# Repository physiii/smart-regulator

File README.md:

## This repository contains the code, schematic, and layout for a wifi controlled and monitored 5V 3A regulator that works with __open-automation__.

### open-automation is made from a cohesive set of web languages. NodeJS for general processing, socket.io for bidirectional communication. NodeJS is used for generating, setting, and retreiving model (mongodb) data. Websockets is used for transport on microcontrollers. Live token based streaming with JSMPEG decoding on camera devices. Web interface is angularjs. Android app for location beacons. Now supports streaming from behind routers, this is done through websockets; so no port forwarding necessary!

### Can be used for controlling cameras, dead bolts, garage openers, lights, thermostats, media, glass break, and a customizable alert system.

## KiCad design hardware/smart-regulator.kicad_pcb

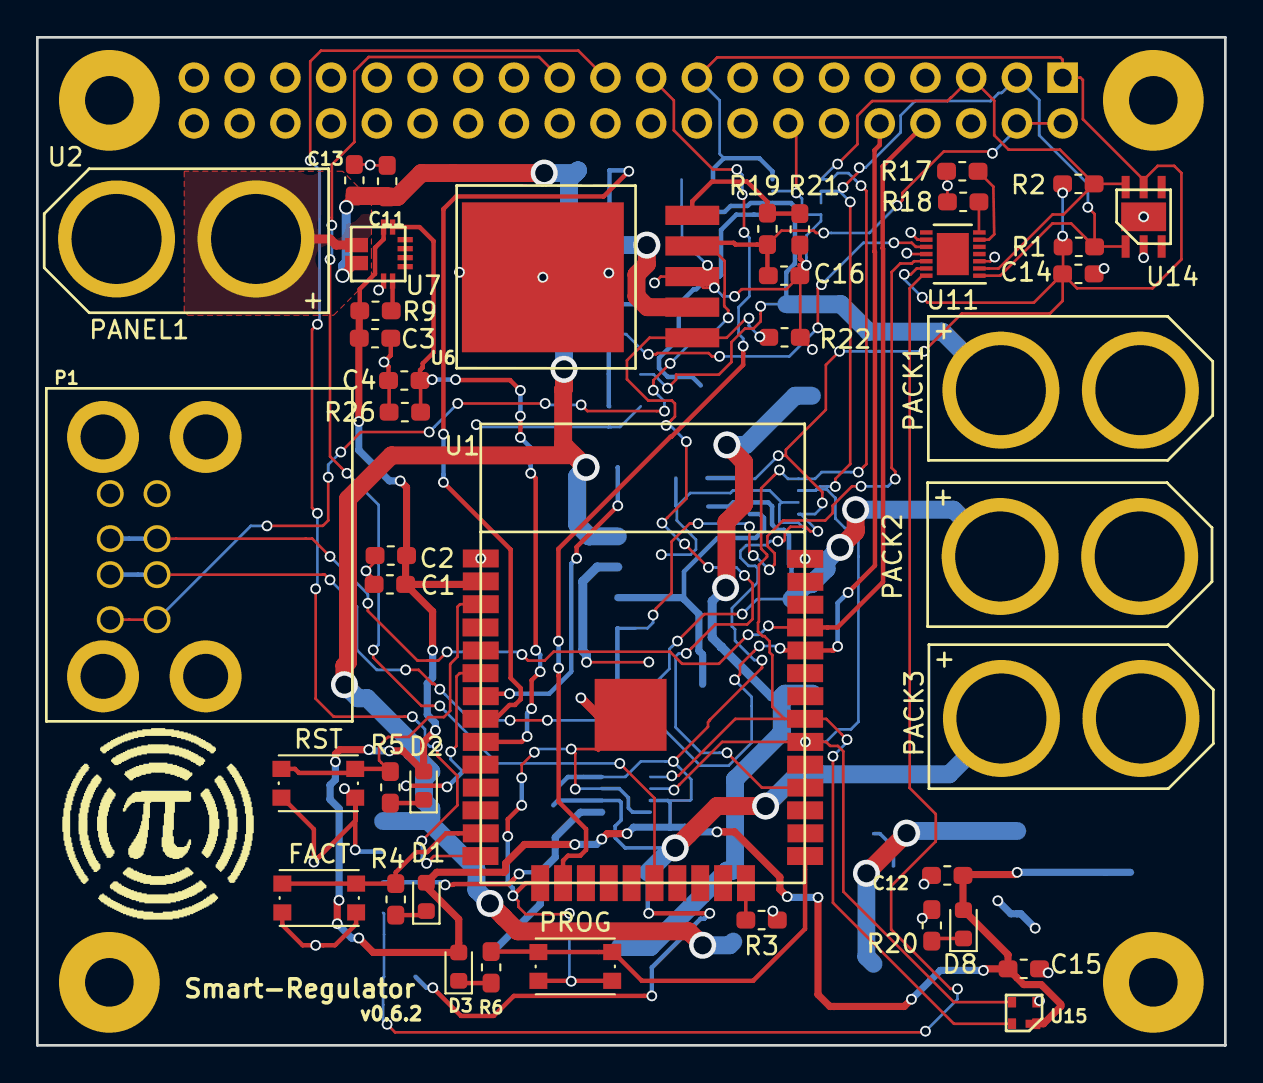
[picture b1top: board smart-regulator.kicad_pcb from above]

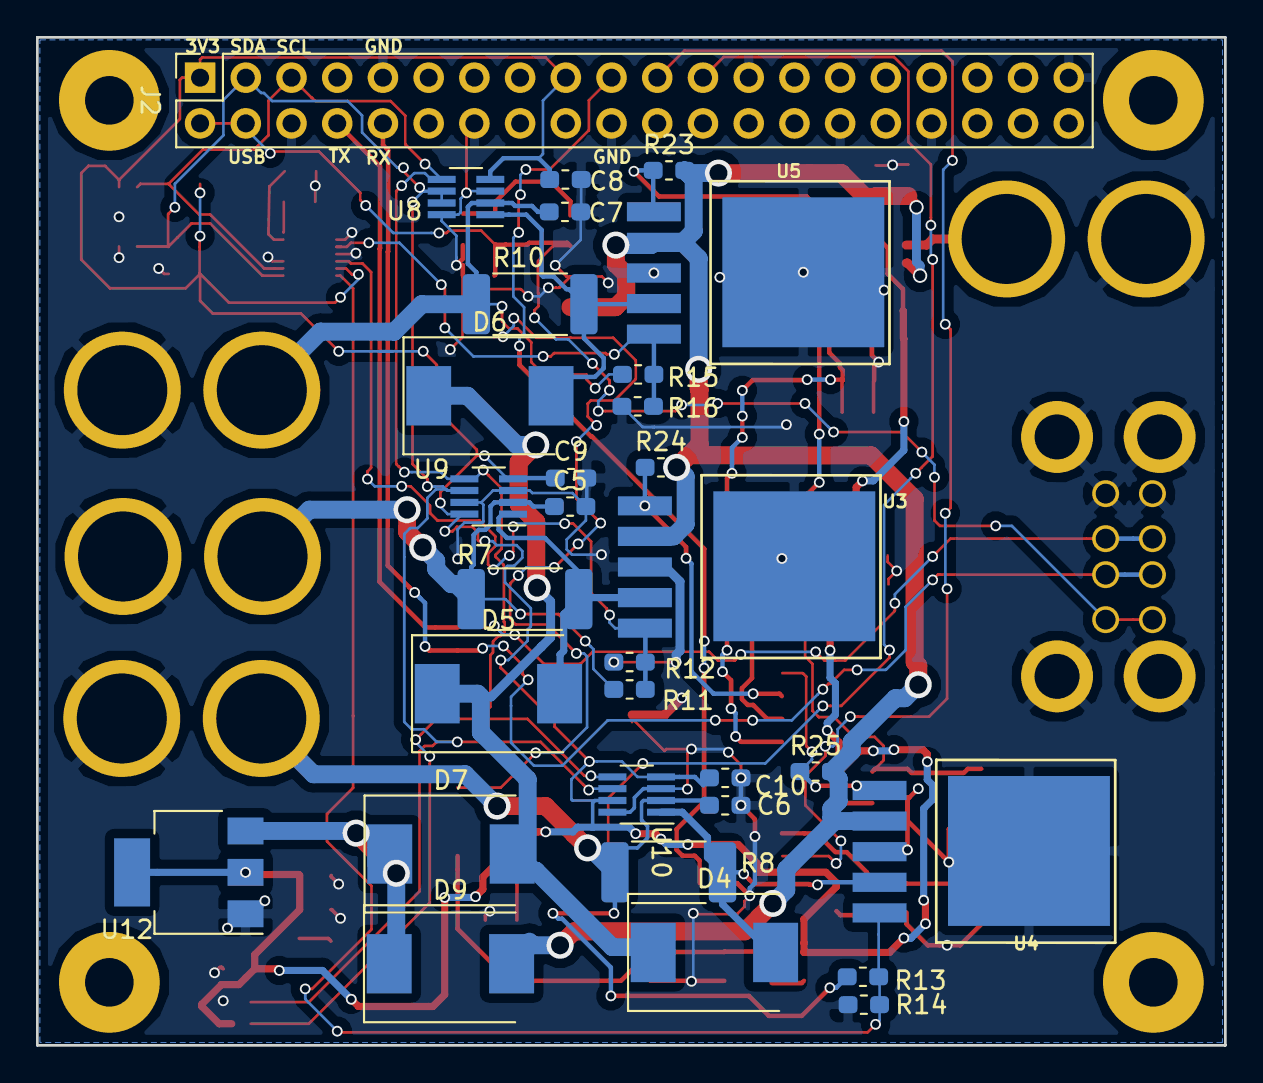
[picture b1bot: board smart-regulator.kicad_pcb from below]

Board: 2 copper layers, 66.0 x 56.0 mm, 75 parts (31 on the bottom side), 40 nets.

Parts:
C1, C4, C5, C6, C7, C11, C16: C_10uF; C_0603_1608Metric_Pad1.05x0.95mm_HandSolder
C2, C13: C_1uF; C_0603_1608Metric_Pad1.05x0.95mm_HandSolder
C3, C8, C9, C10, C14, C15: C_0.1uF; C_0603_1608Metric_Pad1.05x0.95mm_HandSolder
C12: 4.7uF; C_0603_1608Metric_Pad1.05x0.95mm_HandSolder
D1, D2, D3, D8: LED-0603-R; LED_0603_1608Metric_Pad0.88x0.95mm_HandSolder
D4, D5, D6, D7, D9: D; D_SMC
FACT: SW_PUSH; SW_SPST_KMR2
J2: Conn_02x20_Odd_Even; PinSocket_2x20_P2.54mm_Vertical
LOGO: pyfi_symbol
P1: USB_A_2
PACK1, PACK2, PACK3: CONN_01X02; XT60
PANEL1: CONN_01X02; XT60
PROG: SW_PUSH; SW_SPST_KMR2
R1, R2, R3, R4, R5, R6, R11, R12, R13, R14, R15, R16, R19, R20, R21, R22, R23, R24, R25, R26: R_10k; R_0603_1608Metric_Pad1.05x0.95mm_HandSolder
R7, R8, R10: R_10m; R_2512_6332Metric_Pad1.52x3.35mm_HandSolder
R9, R17, R18: R_1k; R_0603_1608Metric_Pad1.05x0.95mm_HandSolder
RST: SW_PUSH; SW_SPST_KMR2
U1: ESP-WROOM-32
U2: housing-mounts; Pi Mount
U3, U4, U5, U6: MIC29302; Regulator-LM2576
U7: ACS712ELCTR-05B-T_NRND; ACS711
U8, U9, U10: Power-Monitor-INA219; SOT-23-8_Handsoldering
U11: DAC; DFN-14-1EP_3x3mm_P0.4mm_EP1.78x2.35mm
U12: ZLDO1117G33TA; SOT-223
U14: SI7006-A20; SI7020-A20
U15: TSL45315CL; LIGHT-SENSOR-TSL45315CL

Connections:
3V3: C1.1, C2.1, C3.1, C8.2, C9.2, C10.2, C12.1, C14.1, C15.1, D1.2, D2.2, D3.2, D8.2, J2.1, J2.17, R1.2, R2.2, R9.1, U1.2, U7.12, U8.4, U9.4, U9.8, U10.4, U10.7, U11.13, U12.2, U12.4, U14.5, U15.1
/EN: R5.2, RST.1, U1.3
/FACTORY: FACT.1, R4.2, U1.13
/I02: R3.2, U1.24
/PACK1: C7.1, PACK1.1, R10.2, R15.1, U8.2
/PACK2: C5.1, PACK2.1, R7.2, R11.1, U9.2
/PACK3: C6.1, PACK3.1, R8.2, R13.1, U10.2
/PROG: PROG.1, R6.2, U1.25
/Power/OUT1: R15.2, R16.1, U5.5, U11.10
/Power/OUT2: R11.2, R12.1, U3.5, U11.12
/Power/OUT3: R13.2, R14.1, U4.5, U11.14
/Power/REG1_PRE: D6.2, R10.1, U5.4, U8.1
/Power/REG2_PRE: D5.2, R7.1, U3.4, U9.1
/Power/REG3_PRE: D4.2, R8.1, U4.4, U10.1
/Power/REG_POWER: C11.1, C13.1, D9.2, R23.2, R24.2, R25.2, U3.2, U4.2, U5.2, U6.2, U7.3
/REG1_EN: R23.1, U1.8, U5.1
/REG2_EN: R24.1, U1.7, U3.1
/REG3_EN: R25.1, U1.6, U4.1
/RXD: J2.10, P1.4, P1.6, U1.34
/SCL: J2.5, R2.1, U1.31, U8.5, U9.5, U10.5, U11.2, U14.6, U15.4
/SDA: J2.3, R1.1, U1.30, U8.6, U8.7, U9.6, U10.6, U11.1, U14.1, U15.3
/TXD: J2.8, P1.3, P1.5, U1.35
/USB_EN: R22.1, U1.28, U6.1
/V_MAIN: D4.1, D5.1, D6.1, D7.2
/V_PANEL: PANEL1.1, U7.1
/V_USB: C16.1, J2.2, J2.4, P1.2, R19.1, U6.4
/microcontroller/MISO: J2.21, U1.14
/microcontroller/MOSI: J2.19, U1.16
/microcontroller/SCLK: J2.23, U1.20
GND: C1.2, C2.2, C3.2, C4.2, C5.2, C6.2, C7.2, C8.1, C9.1, C10.1, C11.2, C12.2, C13.2, C14.2, C15.2, C16.2, FACT.2, J2.6, J2.9, J2.14, J2.20, J2.25, J2.30, J2.34, J2.39, P1.1, P1.7, PACK1.2, PACK2.2, PACK3.2, PANEL1.2, PROG.2, R3.1, R12.2, R14.2, R16.2, R17.2, R18.2, R20.2, R21.2, R22.2, R26.2, RST.2, U1.1, U3.3, U4.3, U5.3, U6.3, U7.5, U8.3, U8.8, U9.3, U9.7, U10.3, U10.8, U11.3, U11.9, U11.11, U12.1, U14.2, U15.2
MAIN_CURRENT_SENSE: C4.1, R26.1, U1.9, U7.11
unnamed: D1.1, R4.1
unnamed: D2.1, R5.1
unnamed: D3.1, R6.1
unnamed: D7.1, D9.1, U12.3
unnamed: D8.1, R20.1
unnamed: R9.2, U7.6
unnamed: R17.1, U11.6
unnamed: R18.1, U11.7
unnamed: R19.2, R21.1, U6.5

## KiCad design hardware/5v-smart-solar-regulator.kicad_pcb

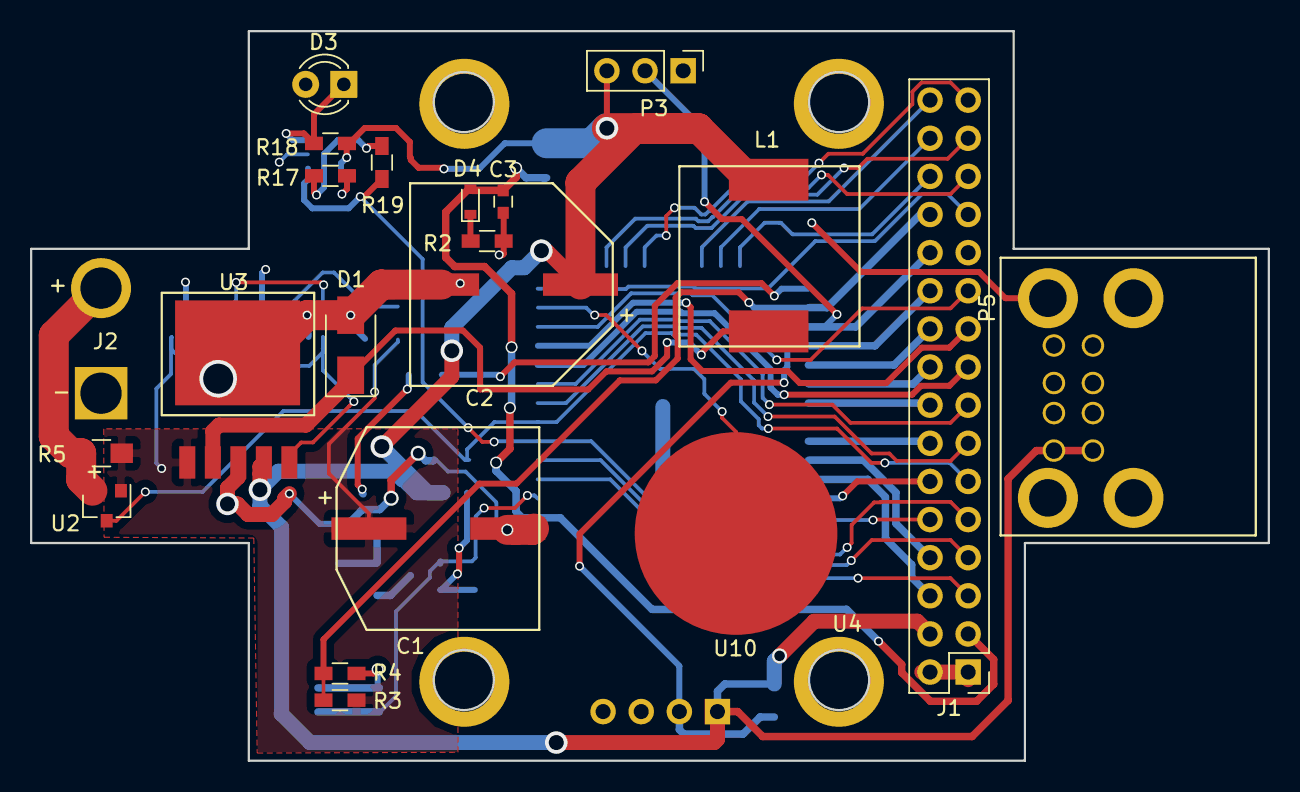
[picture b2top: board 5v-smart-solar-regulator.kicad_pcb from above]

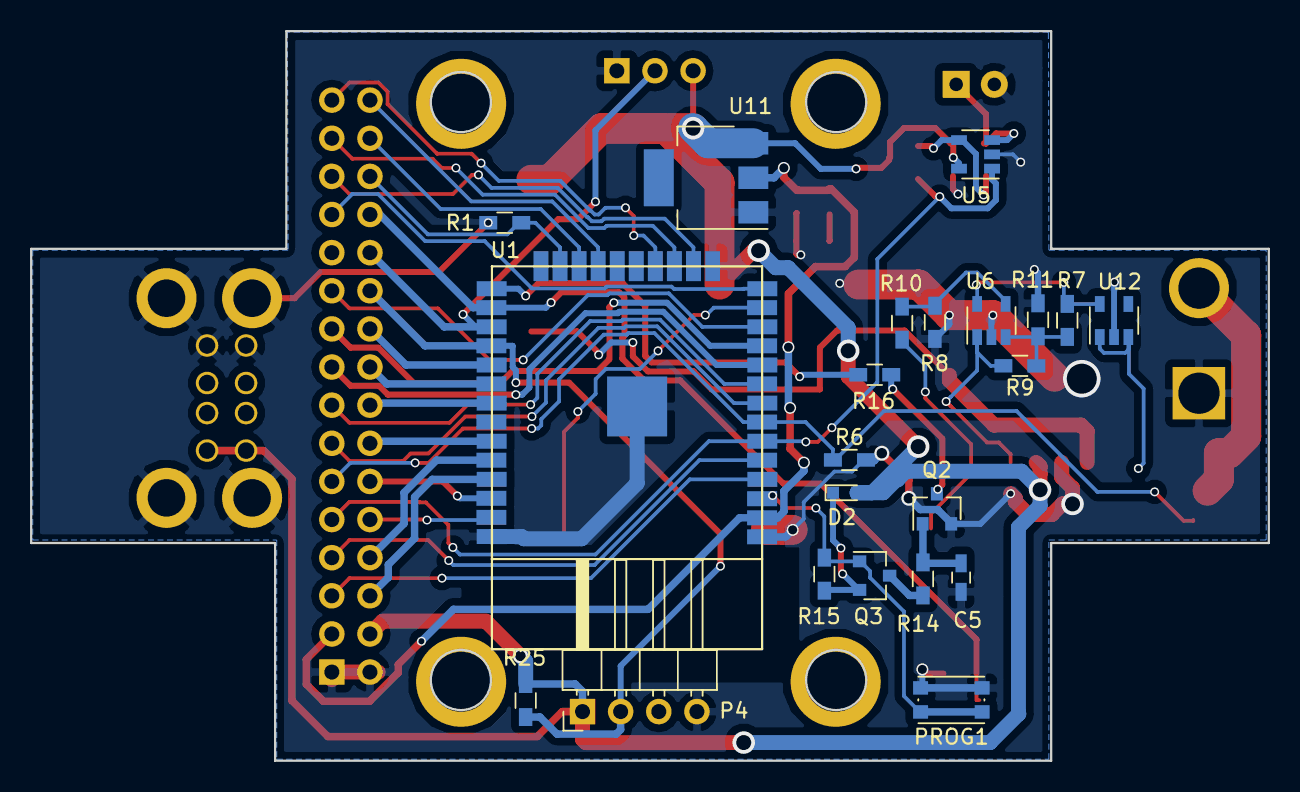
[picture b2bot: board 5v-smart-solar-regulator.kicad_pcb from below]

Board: 2 copper layers, 82.5 x 48.6 mm, 44 parts (22 on the bottom side), 47 nets.

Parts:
C1: 100uF; smd-cap-13.5
C2: 1000uF; smd-cap-13.5
C3: 4.7uF; C_0603
C5: 4.7uF; C_0603_HandSoldering
D1: D_Schottky; D_SMA
D2: LED; LED_0603
D3: LED; LED_D3.0mm
D4: LED; D_0603
J1: CONN_02X16; Pin_Header_Straight_2x16_Pitch2.54mm
J2: CONN_01X02; battery_input
L1: 47uH; Inductor-SRR1210
P3: CONN_01X03; PIR-SR501
P4: CONN_01X04; Pin_Header_Angled_1x04_Pitch2.54mm
P5: USB_A_2
PROG1: SW_PUSH; SW_SPST_KMR2
Q2: Q_NMOS_GSD; SOT-23
Q3: Q_PMOS_GSD; SOT-23
R1, R25: 10K; R_0603_HandSoldering
R2, R14, R15, R16: 1K; R_0603_HandSoldering
R3, R10: 100K; R_0603_HandSoldering
R4: 25K; R_0603_HandSoldering
R5: 50m; R_0805_HandSoldering
R6: 5K; R_0603_HandSoldering
R7, R11: 82K; R_0603_HandSoldering
R8: 30K; R_0603_HandSoldering
R9: 3M; R_0603_HandSoldering
R17: 22K; R_0603_HandSoldering
R18: 1M; R_0603_HandSoldering
R19: 180K; R_0603_HandSoldering
U1: ESP-WROOM-32
U2: ZXCT1107; Current_sense-ZXCT1107
U3: LM2576; Regulator-LM2576
U4: housing-mounts; enclosure-25x38
U5, U6: OPA344NA/3K; SOT-23-5
U10: touchpad; touch-pad
U11: SPX1117M3-L-3-3/TR; SOT-223
U12: AP2204K-5.0TRG1; SOT-23-5

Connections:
3v3: C3.1, D4.2, J1.3, U1.2, U11.2
5V: C2.1, D2.2, J1.4, L1.2, P3.3, P4.1, P5.2, R18.2, R25.2, U3.4, U5.5, U11.3
5V_ref: R7.1, U6.5, U12.5
BATTERY: J2.1, R5.1, U2.3
EN: PROG1.1, Q3.1, R15.2, U1.3
GND: C1.2, C2.2, C3.2, C5.1, D1.2, D3.2, J1.1, J1.2, J2.2, P3.1, P4.4, P5.1, P5.7, PROG1.2, Q2.2, R1.2, R2.2, R4.1, R6.1, R8.2, R11.2, R17.2, U1.1, U3.3, U5.2, U6.2, U11.1, U12.2
IO0: R16.1, U1.25
IO4: J1.26, R3.2, R4.2, U1.26
IO5: J1.20, U1.29
IO12: J1.25, U1.14
IO13: J1.27, U1.16
IO14: U1.13, U10.1
IO15: J1.28, R1.1, U1.23
IO16: J1.24, P3.2, U1.27
IO17: J1.22, P4.2, R25.1, U1.28
IO18: J1.18, U1.30
IO19: J1.16, U1.31
IO21: J1.14, U1.33
IO22: J1.12, U1.36
IO23: J1.10, U1.37
IO25: J1.17, U1.10
IO26: J1.19, U1.11
IO27: J1.21, U1.12
IO32: J1.13, U1.8
IO33: J1.15, U1.9
IO34: J1.9, R19.2, U1.6, U5.1
IO35: J1.11, R6.2, U1.7, U2.1
unnamed: C5.2, Q2.1, R14.2
unnamed: D1.1, L1.1, U3.2
unnamed: D2.1, Q3.2, R15.1
unnamed: D3.1, R18.1, U5.3
unnamed: D4.1, R2.1
unnamed: Q2.3, R16.2
unnamed: Q3.3, R14.1
unnamed: R8.1, R10.2, U6.4
unnamed: R7.2, R9.1, R11.1, U6.3
unnamed: R17.1, R19.1, U5.4
RXD: J1.8, U1.34
SD0: J1.32, U1.21
SD1: J1.30, U1.22
SD2: J1.29, U1.17
SD3: J1.31, U1.18
SENSOR_VN: J1.7, U1.5
SENSOR_VP: J1.5, U1.4
TXD: J1.6, U1.35
Vin: C1.1, R3.1, R5.2, R10.1, U2.2, U3.1, U12.1, U12.3
power_EN: R9.2, U3.5, U6.1

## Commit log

2018-07-02 regulator ya know
2018-07-03 dac and diodes
2018-07-03 additional components
2018-07-06 layout complete bitches
2018-07-16 multifile update
2018-07-19 traces complete
2018-07-20 parts
2018-07-31 re-layout
2018-08-01 silkscreen
2018-08-01 series ender
2018-08-02 rewire
2018-08-02 corrected error on schem/layout
2018-08-20 update before try #3
2018-08-22 fixed footprint missmatch on diodes/final touchups
